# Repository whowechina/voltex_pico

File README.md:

# Voltex Pico - Sound Voltex Style Mini Controller
[点这里可以切换到中文版](README_CN.md)

Features:
* It's ultra thin but closely replicates the feel of the arcade controller.
* Supports both Hall Effect (magnetic) switches and regular mechanical switches.
* Utilizing my new innovation: stabilizer mechanics for big and thin buttons.
* Hall Effect knobs.
* Full HID light support.
* Command line for configurations.
* Two size versions: Voltex Jumbo is arcade size, Voltex Pico is about 85% of that.
* All source files open.

Thanks to many respected guys/companies who made their tools or materials free or open source (KiCad, OnShape, InkScape, Raspberry things).

Special thanks to community projects and developers.
And also these projects:
* RP_Silicon_KiCad: https://github.com/HeadBoffin/RP_Silicon_KiCad
* Type-C: https://github.com/ai03-2725/Type-C.pretty
* USBemani: https://github.com/progmem/usbemani (for the Spoof mode USB descriptor)

## My Other Projects
You can check out my other cool projects.

* Popn Pico: https://github.com/whowechina/popn_pico
* IIDX Pico: https://github.com/whowechina/iidx_pico
* Chu Pico: https://github.com/whowechina/chu_pico
* Mai Pico: https://github.com/whowechina/mai_pico
* Diva Pico: https://github.com/whowechina/diva_pico
* AIC Pico: https://github.com/whowechina/aic_pico
* Groove Pico: https://github.com/whowechina/groove_pico
* Geki Pico: https://github.com/whowechina/geki_pico
* Musec Pico: https://github.com/whowechina/musec_pico
* Ju Pico: https://github.com/whowechina/ju_pico
* Bishi Pico: https://github.com/whowechina/bishi_pico
* Nos Pico: https://github.com/whowechina/nos_pico
* Voltex Pico: https://github.com/whowechina/voltex_pico
* Chord Pico: https://github.com/whowechina/chord_pico
* Dance Pico: https://github.com/whowechina/dance_pico
* Arcade Pico: https://github.com/whowechina/arcade_pico

## **Disclaimer** ##
I made this project in my personal time with no financial benefit or sponsorship. I will continue to improve the project. I have done my best to ensure that everything is accurate and functional, there's always a chance that mistakes may occur. I cannot be held responsible for any loss of your time or money that may result from using this open source project. Thank you for your understanding.

## About the License
It's CC-NC. So DIY for yourself and for your friend, don't make money from it. And plagiarism that doesn’t even dare to mention the original author is not acceptable. Please note that pooling orders and group buying for raw materials is acceptable. Selling off any leftover components without profit is also acceptable.

If you're interested in buying from me or some kind of commercial use, please contact me (Discord, QQ group, Wechat group or leave your contact in issue section).

## My Discord Invitation
https://discord.gg/M8f2PPQFEA

## HOW TO BUILD
### PCB and Components
* Go JLCPCB and make order with the gerber zip files (latest `Production\PCB\voltex_xxx_vvv.zip`), regular FR-4 board, black or white color, **1.6mm** thickness. For Voltex Jumbo, you need 2 boards.  
* 1x Rasberry Pico Pi Pico or pin-to-pin compatible clones (U1).  
  https://www.raspberrypi.com/products/raspberry-pi-pico
* 1x USB Type-C socket (918-418K2023S40001 or KH-TYPE-C-16P)
* 50x 0603 0.1uF capacitors (all capacitors on the PCB, most of them are optional).
* 4x 0603 5.1kohm resistors (R1, R2, R3, R4).
* 2x ALPS SKHHBVA010 or compatible (6\*6\*7mm) tactile switches for the AUX buttons.
* 22x Reverse Mount WS2812B-3528 RGB LEDs (all corresponding PCB footprints).
* 18x WS2812B-4020 side emitting RGB LEDs (DL1-DL9, DR1-DR9).
* 2x TMAG-5273A1 or TMAG5273A2, in SOT23-6 (U3, U4).

* For Voltex Pico only:
  * 12x U-shape 2U stabilizer steel wires, you can also harvest them from regular 2U MX stabilizers.
  * 1x Kailh Choc switch for the START button (B7), and a matching blank translucent keycap.
  * 4x 1.0mm 6-pin FPC connectors, bottom contact, front flip.
  * 2x 1.0mm 6-pin FPC cables, 25mm to 30mm long. Longer ones are also fine if bent properly.

* For Voltex Jumbo only:
  * 4x U-shape 2U stabilizer steel wires, you can also harvest them from regular 2U MX stabilizers.
  * 8x U-shape 3U stabilizer steel wires, they might bedifficult to find, you can use 2U instead (use correct 3D printing parts accordingly).
  * 8x SH1.0 4P horizontal surface mount connector.
  * 2x Kailh Choc switch for the START buttons (B4), and matching blank translucent keycaps.
  * 4x SH1.0 4P silicone cables, pin-to-pin straight-through (also called reverse orientation), 10cm in length.

* The following is for regular switch build.
  * 6x Kailh Choc low-profile switches. Choose heavy ones (70gf+) for 4 BT buttons, and regular ones (50gf) for 2 FX buttons.

* The following is for Hall Effect switch build.
  * 1x ADG708BRUZ, 8 to 1 analog switch, in TSSOP-16 (U2).
  * 1x LM4040 Shunt Voltage Reference, get one with 2.0, 2.1, or 2.5 reference voltage, in SOT23-3 (U6).
  * 1x LP5907MFX-4.5 or TPS7A2042PDBVR LDO, in SOT23-5 (U7).
  * 6x SS49E or compatible linear Hall Effect sensors, in SOT23-3.
  * 1x 1kohm resistor, 0603 (R5).
  * 1x 50kohm resistor, 0603 (R6).
  * 1x 3.3V Zener diode, in SOD-123 or SOD-123F, such as BZT52H-C3V3 (Z1).
  * 6x low profile magnetic switches.
  * 4x heavy springs (60gF+) for low-profile switches, to replace the original ones in 4 BT switches. You may buy or harvest them from Kailh Choc heavy switches.
  * For Voltex Jumbo, solder either "HALL" or "BT" SH1.0 connector on left side PCB, depending on whether you are using Hall Effect version or regular switch version.

* Here's a soldered Voltex Pico PCB for reference (there might be changes in newer versions of PCB). It's a Hall Effect switch build.  

* **Important notes for Voltex Jumbo.** For left side, only solder the components with no "R" mark, or only solder the component at the side with no "R" mark by the footprint; for right side, only solder the components with the "R" mark, or only solder the component at the side with the "R" mark by the footprint.

* Here's a set of soldered Voltex Jumbo PCBs for reference (there might be changes in newer versions of PCB). It's a Hall Effect switch build. The order is left top, right top, left bottom, right bottom.  

### Important Tips for Soldering
* Be careful of 2 pin holes. It's a common oversight to either forget to solder them or to leave air bubbles during the process. To avoid this, solder slowly from one side of the hole, using minimal solder wire and a generous amount of flux.
* Reverse mount LEDs are soldered at the bottom side of the PCB.
* On Voltex Pico, D4 actually requires a regular WS2812B-3528 RGB LED, not a reverse mount one. We can make one from a reverse mount one. Just bend the 4 feet to the bottom and it becomes a regular WS2812B-3528.  
  
* Be careful with WS2812B-4020 orientation. DL1 to DL4, and DR1 to DR4 are side facing, while the DL5 to DL9 and DR5 to DR9 are top facing. 
* You don't need to solder all the capacitors, it's fine to just solder the ones right beside ICs.
* Z1 is to protect the Pico from excessive voltage, don't ignore it.
* There are many LDOs and shunt voltage reference models, as long as they have the same form factor, pinout and voltage, you can use them. Best LDO voltages are 4.0 to 4.5V, they should not go higher than 4.5V, as the USB voltage under load could be lower than it. The shunt voltage reference should be 2.0 to 2.5V, roughly half of the LDO voltage.
* For regular switch build, you need to solder the switches onto the PCB. For Hall Effect switch build, you don't need to solder the switches, just make sure the magnets are aligned with the small white circles on the PCB.

### Test the PCB
* You can test the PCB now, put the firmware in.
* Side LEDs and Knob LEDs should light up in a rainbow pattern.
* Button LEDs respond to the button presses (magnetic switches need to be temporarily put on and calibrated).
* Voltex Pico should be recognized as a USB HID device, here's the test page.  
  https://whowechina.github.io/iidx_pico/Tools/gamepad_test.html
* Move a magnetic screwdriver tip close to the TMAG5273 sensor, you'll notice the corresponding axis move in the test page. Please check both sensors.

### Sensor PCB Separation and Soldering for Voltex Pico
* If everything works fine, you can cut off (or even bend and snap) 2 small sensor boards from the main board.
* Connect the sensor PCBs to the main PCB using FPC cables. Older PCB revisions do not have FPC connectors, so solder short flexible wires instead.  

### Connecting Left and Right Side PCBs for Voltex Jumbo
* Use the SH1.0 4P silicone cables to connect the left and right side PCBs, following the markings on the PCBs.
* Right side "HALL_BT" goes to either "HALL" or "BT" at the left side PCB, depending on your build type.
* Cables should go through the hinge silicone tube mentioned later.

### 3D Printing
#### General
* PLA or PETG.
* Layer height: 0.2mm
* Support: No, unless mentioned.
* Files are always in millimeter unit, not inch.
* Description for the parts is mainly based on Voltex Pico. But it's similar for Voltex Jumbo, so separate instructions are not provided.
* Files starting with "Voltex Pico" are for Voltex Pico, and files starting with "Voltex Jumbo" are for Voltex Jumbo.

* For Voltex Pico, files with `_Insert` in their names means it's for heatset inserts. For Voltex Jumbo, there's only heatset insert version.
* For Voltex Jumbo, stabilizer for main BT buttons can either be 2U or 3U, that's why you see file names with `_2U` or `_3U` in them. 3U is strongly recommended for much better feel.

#### 2x Knob Parts
* Knob: `Production\3DPrint\* - Knob.stl`, clear, semi-transparent. Print it upside down. 
* Bearing Fixer: `Production\3DPrint\* - Bearing Fixer.stl`.
* Magnet Seat: `Production\3DPrint\* - Magnet Seat.stl`.

#### Button Parts
For regular switch build, choose Choc V1 or Choc v2 keycaps according to your switch type. For Hall Effect switch build, always choose Choc V2 ones.
**For all button keycaps, print them upside down.**
Note that if your switches are a little taller than usual, you need to use the `*_TallFix.stl` files for Main and FX buttons.

* Main BT: `Production\3DPrint\* - BT Choc V?.stl`, white.
* FX BT: `Production\3DPrint\* - FX-? Choc V?.stl`, smokey transparent. Support required.

#### Wing Parts
* Wing Base: `Production\3DPrint\* - * Wing Base.stl`, black.
* Wing Cover: `Production\3DPrint\* - * Wing Cover.stl`, cyan for the left, orange for the right. Print it upside down.

### Housing Parts
* Base: `Production\3DPrint\* - Base.stl`, black.
* Support: `Production\3DPrint\* - Support.stl`, clear, semi-transparent.
* Panel: `Production\3DPrint\* - Panel Combo.3mf`, white or close-to-white, with logo and patterns in black if you have multi-color system. Print it upside down.  

### Thin Stabilizing Mechanism for Big Button 
Before assembly, I'm going to introduce a new thin stabilizing mechanism for big buttons. I designed it so a slim Voltex Pico is possible.

Stabilizing a button means to make the button not wobble when pressed. A wobbling button is like a seesaw, corners for the button don't go up and down in sync, which makes the button feel bad and not reliable.

Stabilizing a big button is never a problem for arcade, simply because arcade cabs have enough vertical space. They can use so called "tube guide" stabilizing. As long as the tube is long enough (versus the gap between the tube and the shaft), buttons can only move or twist horizontally a little bit, but never wobble like a seesaw. 

Technically, for a slim controller which only has millimeters of vertical space, we can still use tube guide, but such a small tube and shaft will be very difficult to make or harvest, not to mention the sliding surface material. In short words, it's not feasible for DIYers. So we have to use a lever based stabilizing mechanism, like we do in the modern keyboards.

Long keyboard keycaps are "1-dimensional", you only need one stabilizer on their X-axis. But for big arcade buttons - big cicle or square - they need "2-dimensions" of stabilizing. So people just drop in 2 stabilizers, placed perpendicular to each other. Technically this will work. But there come new problems.
  * Vertical space for the stem and the stabilizer is not ideal for a slim controller.
  * Requires accurate keycap stem holes (connecting both the keyswitch and the stabilizer), tiny misalignment can cause stress and bring excessive friction.
  * Both FDM and SLA 3D printing have their own tolerances, which can cause misalignment easily.

So here I'm introducing my way.
First of all, I'm still using a lever-based stabilizing, just like the one in keyboards. A keyboard stabilizer has a U-shape steel lever which stays in two housing units (we call them "stabilizer base"). It rotates around its shaft side and drives two connectors (stems) to move up and down simultaneously.

My change is, remove the housing units and the stems, let the U-shape steel lever drive the keycap directly. With the stems removed, coupling of the keycap and the lever is much more lenient to misalignment; with the housing units removed, the vertical space is much smaller, which is ideal for a slim controller.

The "bearing" for the lever is printed along with the the bottom housing. The keycaps have small holes for the lever arms to go through. A FDM 3D printer can print them easily.

The Voltex Pico uses this new stabilizing mechanism for the big BT buttons as well as the FX buttons.

### Assembly
#### Other components needed
* 6x **M2.5\*(14mm-16mm) screws** for fixing the magnet seat to the knob.
* 8x **M2\*6mm screws** for fixing the bearing (bearing fixer to the wing cover).
* 2x 6702zz (15x21x4mm) bearings for the knobs.
* 2x round magnets, 5mm diameter, 2mm tall, MUST be radially/diametrically magnetized (N-S poles on the curved side).
* Some thin tape (such as acetate tape or high-temp teflon tape) to fix the magnets in place.
* Some 10mm diameter silicone anti-slip pads for the bottom.  
* Some 1mm thick soft felt sheet for damping the knobs.

##### Voltex Pico only
* 6x **M2\*8mm screws** for fixing wing bases to the wing cover, **M2\*6mm** if using heatset inserts.
* 12x **M3\*(4mm-5mm) screws** for fixing the PCB to the base parts.
* 10x **M3\*8mm screws** for fixing the base, wing base, support and the panel. **M3\*6mm** if using heatset inserts.
* 6x **M2\*3mm\*3mm inserts** for the wings (heatset build only).
* 12x **M3\*4mm\*4mm inserts**, 10 for the panel and 2 for wings (heatset build only).  

#### Voltex Jumbo only
* 22x **M2.5\*4mm\*3.5mm inserts (length\*outer diameter)** for the base.
* 10x **M2\*3mm\*3mm heatset inserts** for the wings.
* 14x **M2.5\*(10-11mm) flat head (countersunk) screws** for fixing panels to the bases.
* 8x **M2.5\*6mm screws** for fixing the support to the base.
* 10x **M2\*8mm screws** for fixing wings, screw from bottom side.
* 2x silicone tubes, **inner diameter 25mm, outer diameter 27mm**, cut into **53mm long**, serve as a hinge.

#### Steps for Voltex Pico
1. We'll start with the bearings. They should be inserted into wing parts. Fix them using bearing fixers and M2\*6mm screws.  

2. Cut a ring from the soft felt sheet to dampen the knob. If you feel this is too difficult, you can apply some layers of felt between the knob and the sensor PCB, it works too.   

3. Fix the knob to the bearing with the magnet set and the M2.5 screws (long screws help reinforce the knob shaft). Then put the magnet into the center seat. If you have some thin tape, apply it as a seal so magnet won't fall out.  

4. Put the main PCB into the base part, and sensor PCBs into the wing base parts. Use M3\*(4mm-5mm) screws to fix the PCB to the base parts.  

5. Time to install keycaps to the stabilizer. It's simple, just look at the pictures. You can apply some thin poron pads to dampen the keycap noise, but it's not necessary. Some lubricant can be applied to the lever shaft, this makes the movement smoother. For Hall Effect version, you can use 704 RTV silicone to stick the switches to the PCB, or not - it's totally fine.  

6. Put on the support and the panel. Use M3\*(8mm-10mm) screws to fix the base. Leave the two screws on the wing base empty for now.

7. Put on the wing covers (which already have knobs on them), use M2\*(8mm-10mm) screws to fix them to the wing cover (see the picture for M2 screws). And use M3\*(8mm-10mm) screws on the remaining screw holes (one at each side). Apply silicone pads, they don't look nice but they prevent the controller from sliding on the table.   

8. Congratulations! You have finished the assembly.  

### Notes for Voltex Jumbo
* You need to do left and right sides.
* Screw holes at bottom side for the wings are sealed with thin layer (it's for better screw hole quality), just poke a hole through it using sharp object.
* You need to punch holes for the hinges. Print the helper tool `Voltex Jumbo - Hinge Hole Helper.stl`, it will help you align the holes accurately.
* Cables connecting left and right sides should go through the hinge tube. Extra length of the cables should be managed properly at both ends.
* Hinge tube should be hooked to the columns on both sides before assembly support part.

#### Caution
* Each 3D printer and filament has its own tolerance. If you find the holes on the keycap are too tight, use a needle or knife to enlarge them a little bit.
* Screws are easy to break the 3D printed parts. So don't screw them too tight. When you notice the resistance suddenly increases, stop screwing.

### Firmware
* UF2 file is in `Production\Firmware` folder.
* For the new build, hold the BOOTSEL button while connect the USB to a PC, there will be a disk named "RPI-RP2" show up. Drag the UF2 firmware binary file into it. That's it. There's a small hole at the bottom side, it is facing right to the BOOTSEL button.
* If it's already running Voltex Pico firmware, you can either use "update" in command line or hold down at least 4 buttons while connecting to USB to enter update mode.
* To access the command line, you can use this Web Serial Terminal to connect to the USB serial port of the controller. (Note: "?" is for help)  
  https://whowechina.github.io/iidx_pico/Tools/cli_tool.html

### Usage
* If you built a Hall Effect switch version, you need to calibrate first (`calibrate` command). You can set trigger and reset point in command line.
* Just plug it in and play.
* You can set knob resolution by `knob rate` command.
* You can set trigger and reset point by `trigger` command (only for Hall Effect switch version).
* Dual START buttons are combined with OR by default; use `start <or|and>` to choose OR or AND.
* Hold the left auxiliary button while plugging in to enter Konami spoof mode; the right for regular mode.

## CAD Source File
I'm using OnShape free subscription. It's powerful but it can't archive original designs to local, so I can only share the link here. All model files are exported from this online document.  
  https://cad.onshape.com/documents/757c9485a30088ef0335481e/w/af98e079c47cba7d81086e65/e/9703cb81cc6ed9c6ec563897

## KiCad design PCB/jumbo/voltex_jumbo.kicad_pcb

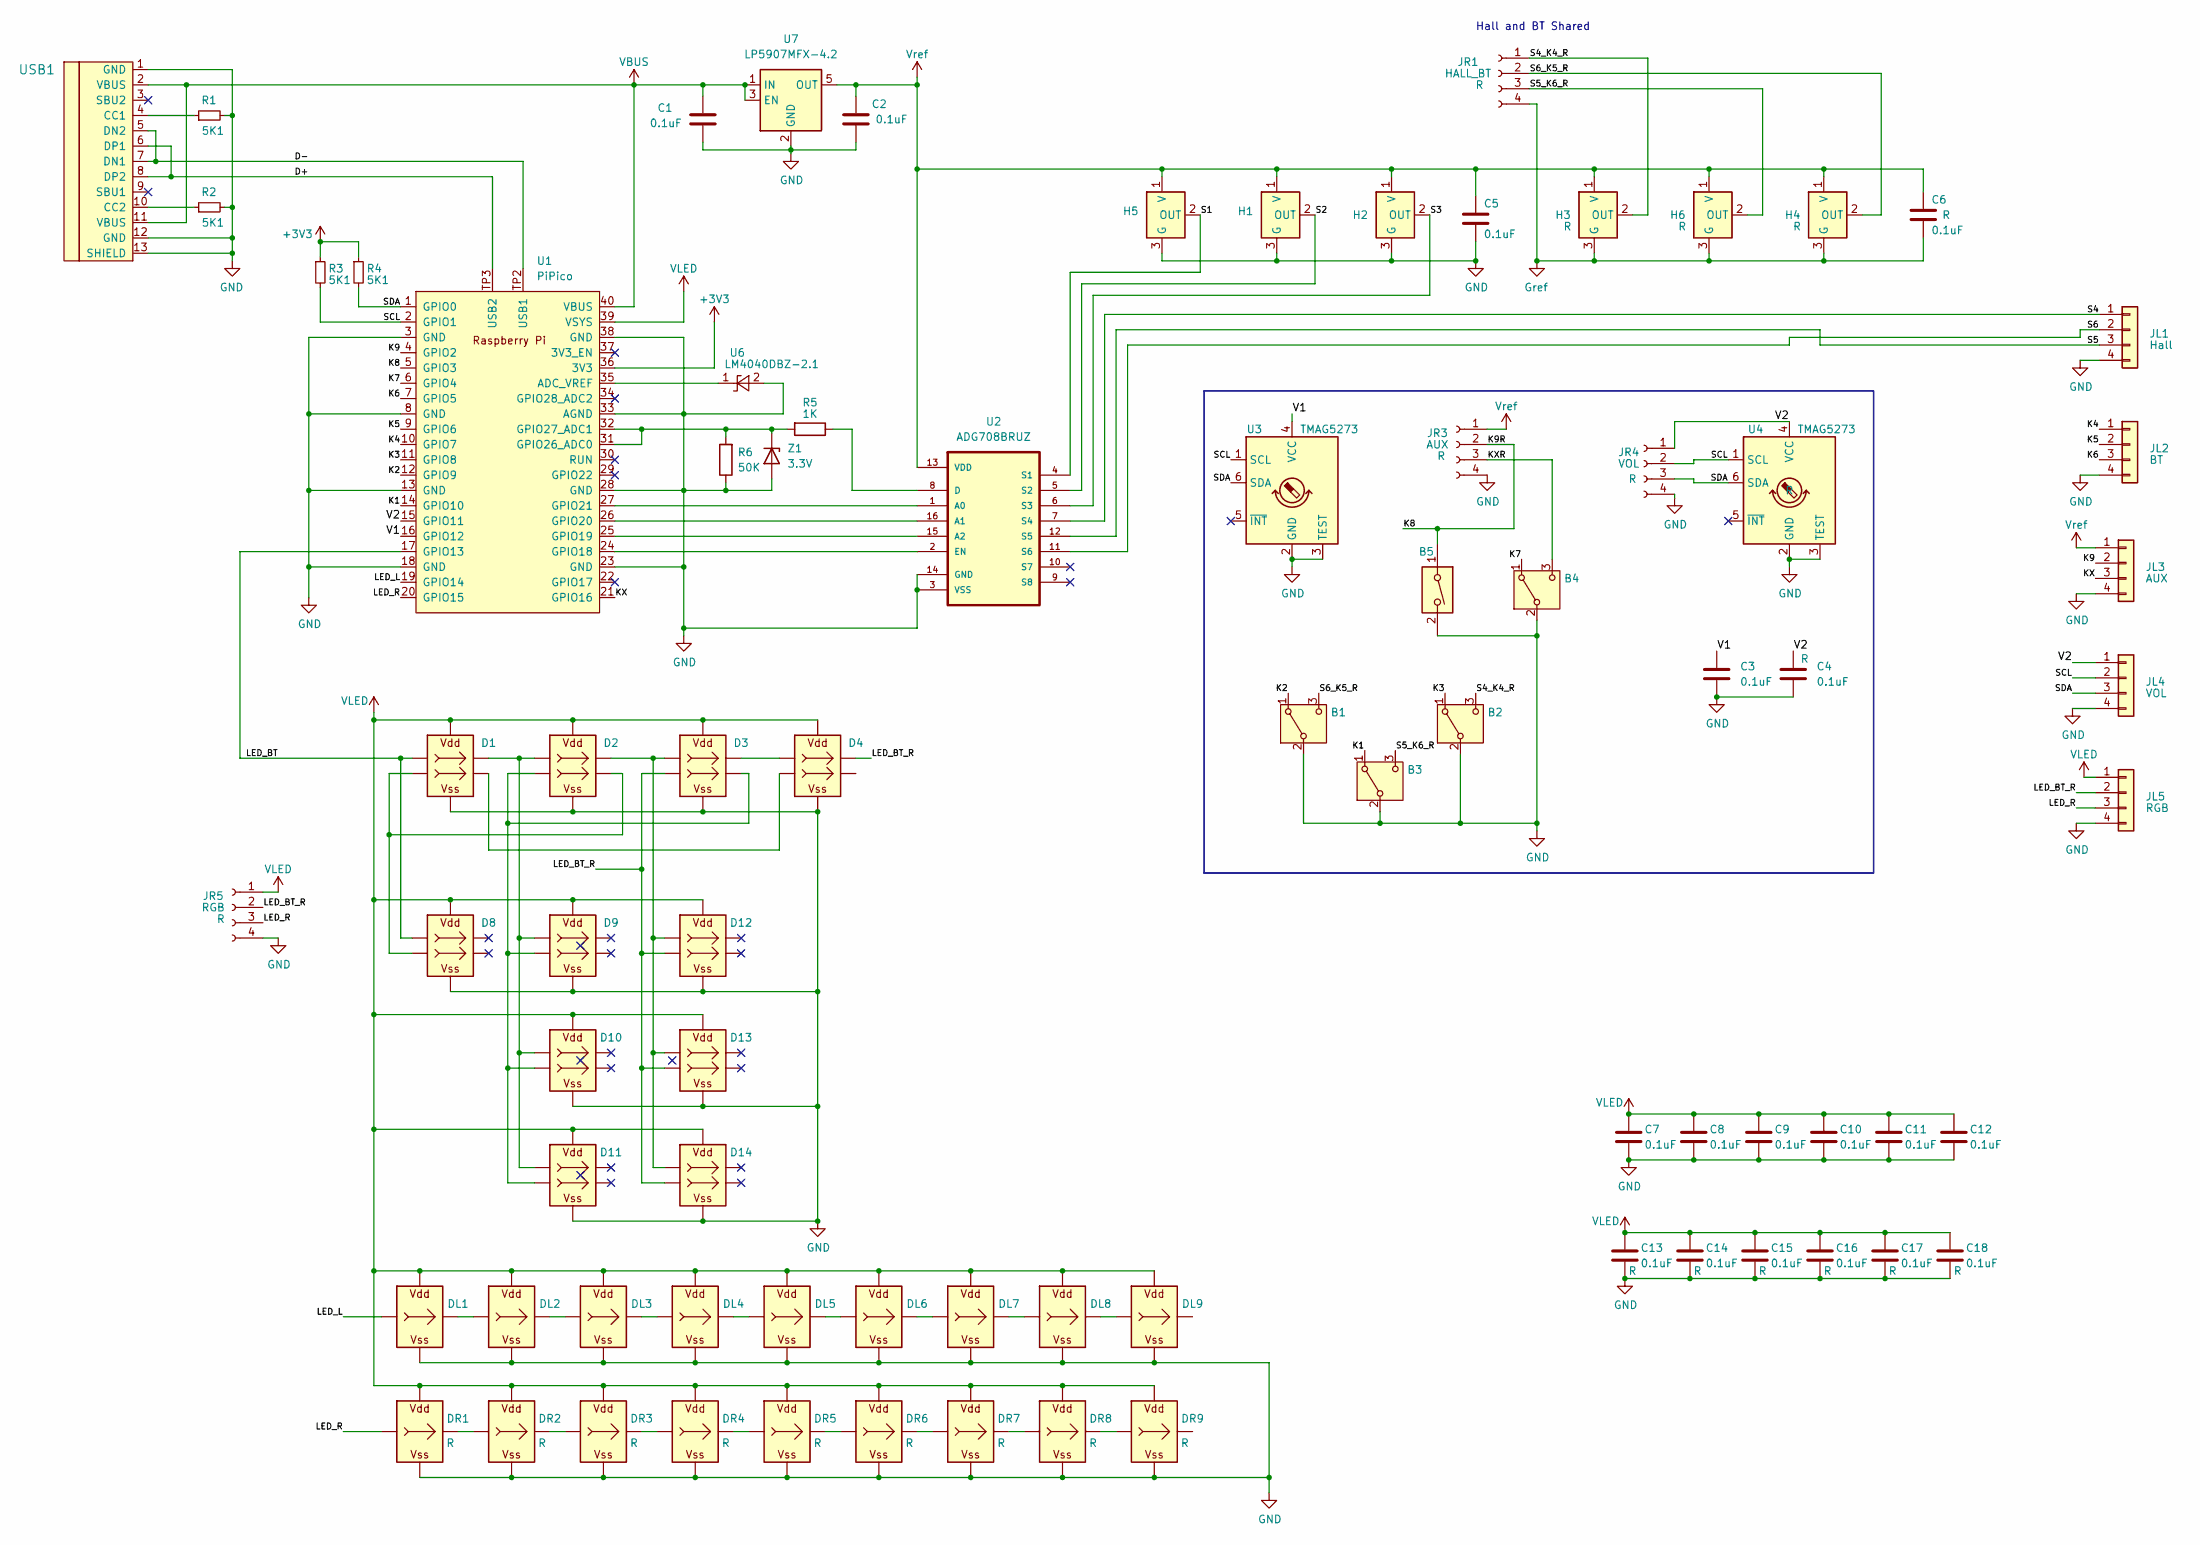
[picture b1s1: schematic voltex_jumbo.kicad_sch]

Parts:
B1, B2, B3: ChocHE; Choc_HE_DoubleSide
B4: ChocHE; Choc_DoubleSide
B5: SW_DIP_x01; SW_SKHHANA010
C1, C2, C3, C4, C5, C6, C7, C8, C9, C10, C11, C12, C13, C14, C15, C16, C17, C18: 0.1uF; C_0603_1608Metric_Pad1.08x0.95mm_HandSolder
D1, D2, D3, D4, D8, D9, D10, D11, D12, D13, D14: WS2812B_Unified; WS2812B-2835_EMBED_DoubleSide
DL1, DL2, DL3, DL4: WS2812B_Unified; WS2812B-4020
DL5, DL6, DL7, DL8, DL9: WS2812B_Unified; WS2812B-4020_UP
DR1, DR2, DR3, DR4: WS2812B_Unified; WS2812B-4020
DR5, DR6, DR7, DR8, DR9: WS2812B_Unified; WS2812B-4020_UP
H1, H2, H3, H4, H5, H6: SS49E_SOT23; SOT-23-FAT
JL1: Hall; SH1.0_4P_Solder_Combo
JL2: BT; SH1.0_4P_Solder_Combo
JL3: AUX; SH1.0_4P_Solder_Combo
JL4: VOL; SH1.0_4P_Solder_Combo
JL5: RGB; SH1.0_4P_Solder_Combo
JR1: HALL_BT; SH1.0_4P_Solder_Combo
JR3: AUX; SH1.0_4P_Solder_Combo
JR4: VOL; SH1.0_4P_Solder_Combo
JR5: RGB; SH1.0_4P_Solder_Combo
R1, R2, R3, R4: 5K1; R_0603_1608Metric_Pad0.98x0.95mm_HandSolder
R5: 1K; R_0603_1608Metric_Pad0.98x0.95mm_HandSolder
R6: 50K; R_0603_1608Metric_Pad0.98x0.95mm_HandSolder
U1: PiPico; RPi_Pico_SMD_No_SWD
U2: ADG708BRUZ; TSSOP-16_4.4x5mm_P0.65mm
U3, U4: TMAG5273; TSOT-23-6_HandSoldering
U6: LM4040DBZ-2.1; SOT-23-FAT
U7: LP5907MFX-4.2; SOT-23-5
USB1: U262-161N-4BVC11; HRO-TYPE-C-31-M-12-Assembly
Z1: 3.3V; D_SOD-123F

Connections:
+3V3: R3.1, R4.1, U1.36 (3V3)
/D+: U1.TP3 (USB2), USB1.6 (DP1), USB1.8 (DP2)
/D-: U1.TP2 (USB1), USB1.5 (DN2), USB1.7 (DN1)
/K1: B3.1 (A), U1.14 (GPIO10)
/K2: B1.1 (A), U1.12 (GPIO9)
/K3: B2.1 (A), U1.11 (GPIO8)
/K4: JL2.1, U1.10 (GPIO7)
/K5: JL2.2, U1.9 (GPIO6)
/K6: JL2.3, U1.7 (GPIO5)
/K7: B4.1 (A), U1.6 (GPIO4)
/K8: B5.1, JR3.2, U1.5 (GPIO3)
/K9: JL3.2, U1.4 (GPIO2)
/KX: JL3.3, U1.21 (GPIO16)
/KXR: B4.3 (C), JR3.3
/LED_BT: D1.I (In), D8.I (In), U1.17 (GPIO13)
/LED_BT_R: D3.IB (InB), D4.O (Out), D12.IB (InB), D13.IB (InB), D14.IB (InB), JL5.2, JR5.2
/LED_L: DL1.I (In), U1.19 (GPIO14)
/LED_R: DR1.I (In), JL5.3, JR5.3, U1.20 (GPIO15)
/S1: H5.2 (OUT), U2.4 (S1)
/S2: H1.2 (OUT), U2.5 (S2)
/S3: H2.2 (OUT), U2.6 (S3)
/S4: JL1.1, U2.7 (S4)
/S4_K4_R: B2.3 (C), H3.2 (OUT), JR1.1
/S5: JL1.3, U2.12 (S5)
/S5_K6_R: B3.3 (C), H6.2 (OUT), JR1.3
/S6: JL1.2, U2.11 (S6)
/S6_K5_R: B1.3 (C), H4.2 (OUT), JR1.2
/SCL: JL4.2, JR4.2, R3.2, U1.2 (GPIO1), U3.1 (SCL), U4.1 (SCL)
/SDA: JL4.3, JR4.3, R4.2, U1.1 (GPIO0), U3.6 (SDA), U4.6 (SDA)
/V1: C3.1, U1.16 (GPIO12), U3.4 (VCC)
/V2: C4.1, JL4.1, JR4.1, U1.15 (GPIO11), U4.4 (VCC)
GND: B1.2 (B), B2.2 (B), B3.2 (B), B4.2 (B), B5.2, C1.2, C2.2, C3.2, C4.2, C5.2, C7.2, C8.2, C9.2, C10.2, C11.2, C12.2, C13.2, C14.2, C15.2, C16.2, C17.2, C18.2, D1.G (VSS), D2.G (VSS), D3.G (VSS), D4.G (VSS), D8.G (VSS), D9.G (VSS), D10.G (VSS), D11.G (VSS), D12.G (VSS), D13.G (VSS), D14.G (VSS), DL1.G (VSS), DL2.G (VSS), DL3.G (VSS), DL4.G (VSS), DL5.G (VSS), DL6.G (VSS), DL7.G (VSS), DL8.G (VSS), DL9.G (VSS), DR1.G (VSS), DR2.G (VSS), DR3.G (VSS), DR4.G (VSS), DR5.G (VSS), DR6.G (VSS), DR7.G (VSS), DR8.G (VSS), DR9.G (VSS), H1.3 (G), H2.3 (G), H5.3 (G), JL1.4, JL2.4, JL3.4, JL4.4, JL5.4, JR3.4, JR4.4, JR5.4, R1.2, R2.2, R6.1, U1.3 (GND), U1.8 (GND), U1.13 (GND), U1.18 (GND), U1.23 (GND), U1.28 (GND), U1.33 (AGND), U1.38 (GND), U2.3 (VSS), U2.14 (GND), U3.2 (GND), U3.3 (TEST), U4.2 (GND), U4.3 (TEST), U6.2 (A), U7.2 (GND), USB1.1 (GND), USB1.12 (GND), USB1.13 (SHIELD), Z1.2 (A)
Gref: C6.2, H3.3 (G), H4.3 (G), H6.3 (G), JR1.4
unnamed: D1.IB (InB), D2.OB (OutB), D8.IB (InB)
unnamed: D1.O (Out), D2.I (In), D9.I (In), D10.I (In), D11.I (In)
unnamed: D1.OB (OutB), D4.IB (InB)
unnamed: D3.O (Out), D4.I (In)
unnamed: D2.IB (InB), D3.OB (OutB), D9.IB (InB), D10.IB (InB), D11.IB (InB)
unnamed: D2.O (Out), D3.I (In), D12.I (In), D13.I (In), D14.I (In)
unnamed: DL1.O (Out), DL2.I (In)
unnamed: DL2.O (Out), DL3.I (In)
unnamed: DL3.O (Out), DL4.I (In)
unnamed: DL4.O (Out), DL5.I (In)
unnamed: DL5.O (Out), DL6.I (In)
unnamed: DL6.O (Out), DL7.I (In)
unnamed: DL7.O (Out), DL8.I (In)
unnamed: DL8.O (Out), DL9.I (In)
unnamed: DR1.O (Out), DR2.I (In)
unnamed: DR2.O (Out), DR3.I (In)
unnamed: DR3.O (Out), DR4.I (In)
unnamed: DR4.O (Out), DR5.I (In)
unnamed: DR5.O (Out), DR6.I (In)
unnamed: DR6.O (Out), DR7.I (In)
unnamed: DR7.O (Out), DR8.I (In)
unnamed: DR8.O (Out), DR9.I (In)
unnamed: U1.35 (ADC_VREF), U6.1 (K)
unnamed: U1.24 (GPIO18), U2.2 (EN)
unnamed: U1.25 (GPIO19), U2.15 (A2)
unnamed: U1.26 (GPIO20), U2.16 (A1)
unnamed: U1.27 (GPIO21), U2.1 (A0)
unnamed: R5.2, R6.2, U1.31 (GPIO26_ADC0), U1.32 (GPIO27_ADC1), Z1.1 (K)
unnamed: R5.1, U2.8 (D)
unnamed: R1.1, USB1.4 (CC1)
unnamed: R2.1, USB1.10 (CC2)
VBUS: C1.1, U1.40 (VBUS), U7.1 (IN), U7.3 (EN), USB1.2 (VBUS), USB1.11 (VBUS)
VLED: C7.1, C8.1, C9.1, C10.1, C11.1, C12.1, C13.1, C14.1, C15.1, C16.1, C17.1, C18.1, D1.V (VDD), D2.V (VDD), D3.V (VDD), D4.V (VDD), D8.V (VDD), D9.V (VDD), D10.V (VDD), D11.V (VDD), D12.V (VDD), D13.V (VDD), D14.V (VDD), DL1.V (VDD), DL2.V (VDD), DL3.V (VDD), DL4.V (VDD), DL5.V (VDD), DL6.V (VDD), DL7.V (VDD), DL8.V (VDD), DL9.V (VDD), DR1.V (VDD), DR2.V (VDD), DR3.V (VDD), DR4.V (VDD), DR5.V (VDD), DR6.V (VDD), DR7.V (VDD), DR8.V (VDD), DR9.V (VDD), JL5.1, JR5.1, U1.39 (VSYS)
Vref: C2.1, C5.1, C6.1, H1.1 (V), H2.1 (V), H3.1 (V), H4.1 (V), H5.1 (V), H6.1 (V), JL3.1, JR3.1, U2.13 (VDD), U7.5 (OUT)

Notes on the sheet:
Hall and BT Shared

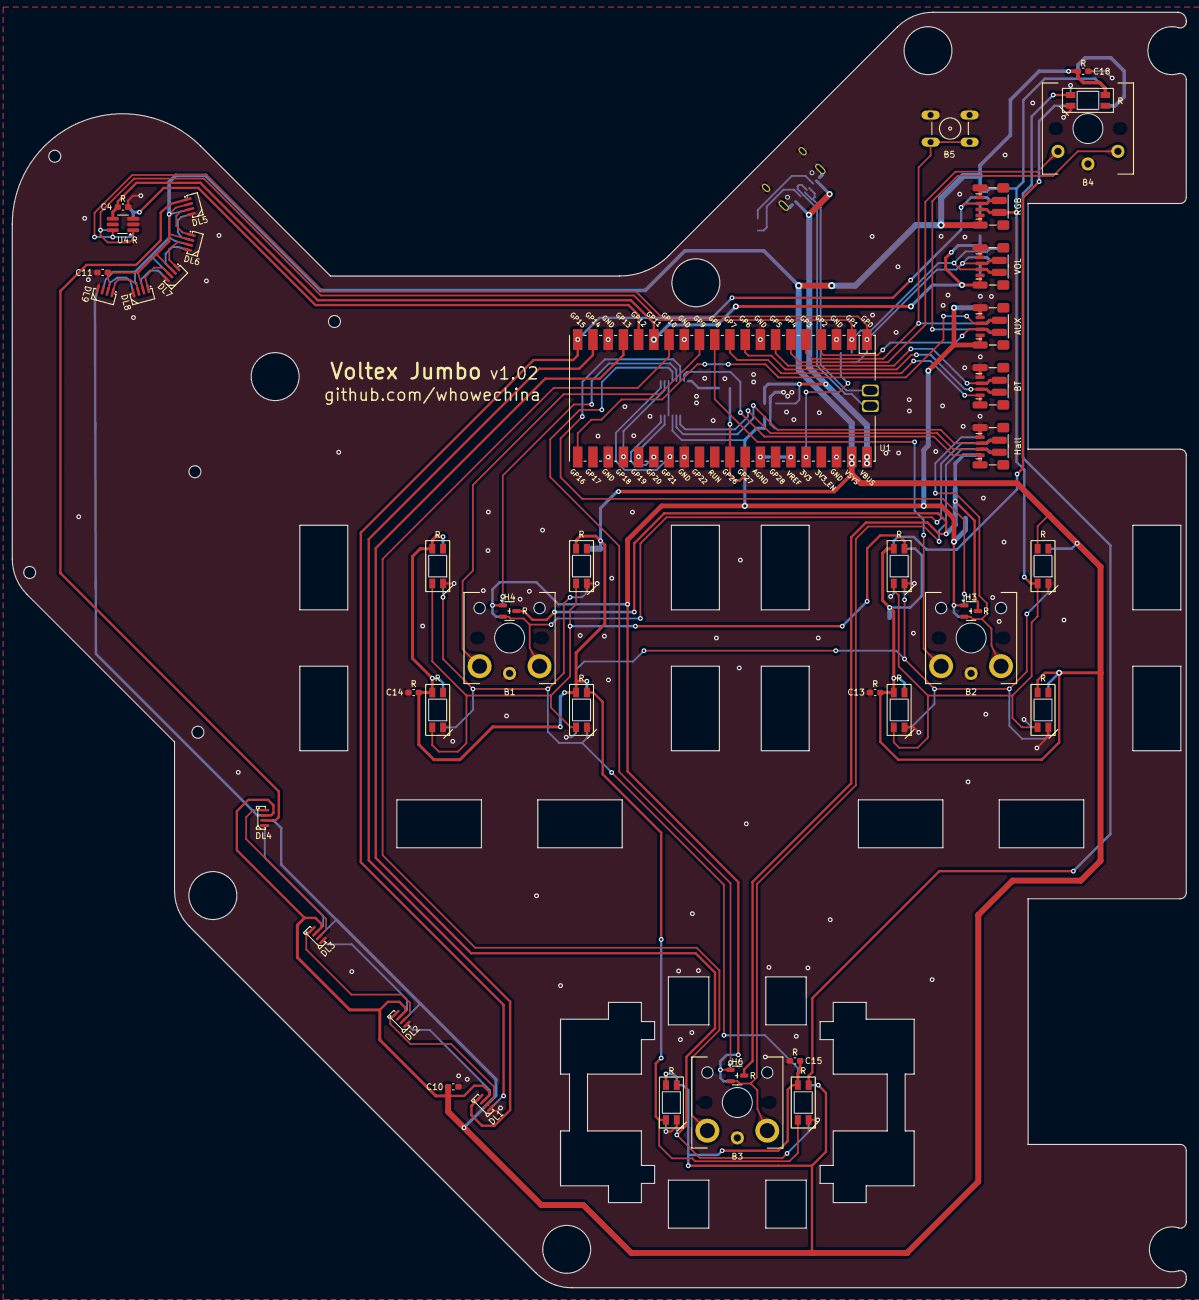
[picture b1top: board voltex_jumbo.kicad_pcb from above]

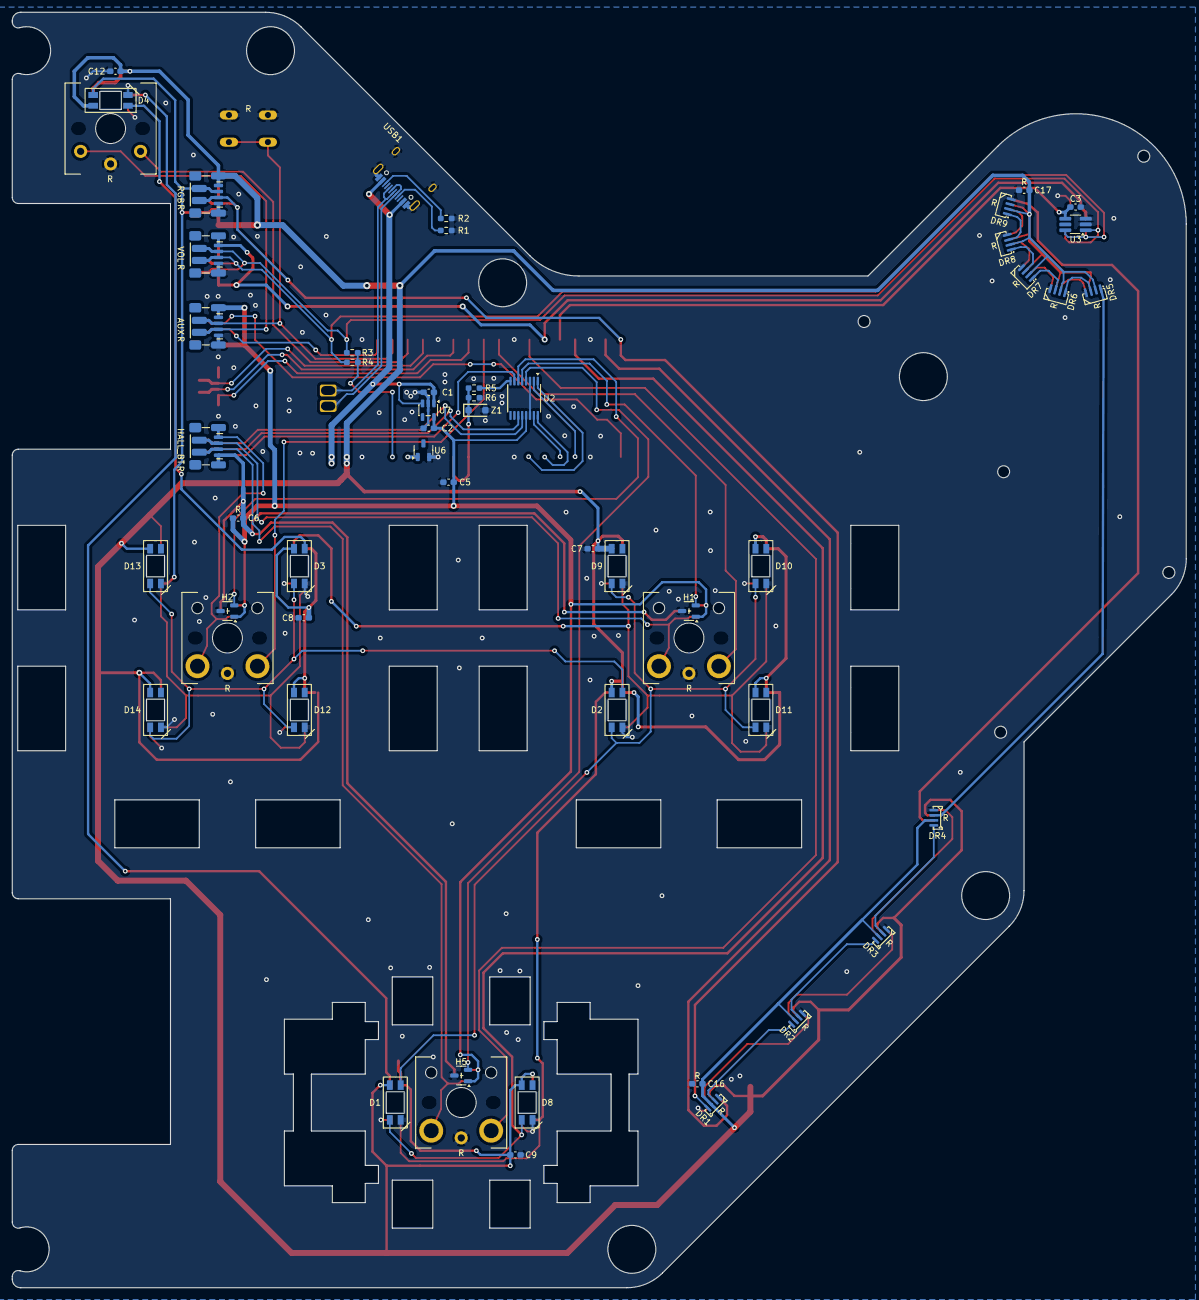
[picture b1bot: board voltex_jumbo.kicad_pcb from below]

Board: 2 copper layers, 195.9 x 212.8 mm, 81 parts (50 on the bottom side), 67 nets.

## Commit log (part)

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2025-05-26 PCB work started
2025-05-27 PCB progress 70%
2025-05-30 PCB done for review
2025-06-02 PCB v1.0
2025-06-04 Firmware begins, light only
2025-06-05 Firmware progress 50%
2025-06-06 HE button works
2025-06-06 Minor wording fix
2025-06-14 HID Light
2025-06-14 PCB v1.11
2025-06-24 Ready to publish
2025-06-25 README in CN
2025-06-25 Notes on magnetic switch
2025-07-03 Fix screw columns in base part
2025-07-05 Ignore hall button when no hall sensor
2025-07-12 Fix bearing model
2025-07-13 Self "cross-referencing"
2025-07-23 Fix LM4040 description
2025-09-18 HE button defaults
2025-09-30 Konami Spoof mode
2025-09-30 Fix housing screw description
2025-09-30 Minor usb descriptor string update
2025-10-01 Fix START key mapping in spoof mode
2025-12-07 Fix trigerring defaults
2025-12-07 Heatset inserts support and fix for taller switches
2025-12-07 Cover spoof mode in readme
2025-12-08 Optimize screw holes
2025-12-12 PCB Pico v1.2 (remove unused parts)
2026-01-01 Recover Bambu Studio ruined file
2026-01-15 Use commercial keycap for START
2026-03-18 PCB v1.3 (use FPC)
2026-03-18 PCB v1.31 (FPC alignment)
2026-03-18 Enlarge base screw hole sinks
2026-03-18 Doc update after PCBv1.3
2026-03-18 PCB image update
2026-03-23 Turn off pico led
2026-06-22 Optimize screw description
2026-06-22 Light shift indication
